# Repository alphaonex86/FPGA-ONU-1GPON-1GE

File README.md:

# FPGA-ONU

An open PON endpoint in one chip: 1 GPON/EPON ONU port (BOSA, to the ISP OLT), 1 SFP
cage (switch SFP, or EPON/GPON OLT module for the OLT role) and 1 Gigabit
Ethernet port, with the MACs, the Ethernet PHY and a RISC-V CPU integrated.
Developed and proven on an FPGA, the final target is an ASIC that holds everything.

## Goals

- GPON ONU MAC: GTC framing, FEC, AES-128 decryption, PLOAM, OMCI, upstream
  burst mode with DBA. EPON MAC (MPCP, OAM) and the OLT role of both.
- 1000BASE-T Ethernet port, PHY integrated in the target ASIC (FPGA phase: a
  copper SFP in an SFP+ cage on our HSMC card for the DE25-Standard; its other
  cage takes an OLT module or a normal SFP).
- SFP cage autodetects the module (EEPROM): 1000BASE-X, EPON OLT or GPON OLT.
- BOSA on board; all optics control (burst, APC, LOS, DDM) in the FPGA/ASIC
  logic; outside only analog: discrete RF transistors, a small ADC/DAC, the APD
  bias boost and passives (FPGA phase: an SY88236L BOSA driver on our HSMC
  card, straight to the DE25-Standard GTS transceivers).
- 32-bit RISC-V CPU (VexiiRiscv, rv32imac, no SIMD, no FPU), high energy
  efficiency, power management (clock gating, sleep states, DVFS); MMU (Sv32)
  so it runs Linux.
- Hardware acceleration (line rate, CPU off the data path): GPON, switching,
  VLAN, PPPoE, IPv4 and IPv6 routing, NAT.
- OpenWrt support: upstream-able riscv32 target, drivers for the GPON MAC and GE port.
- Firmware in an external, socketed, user-programmable flash.
- Behaves on the wire exactly like the stock ONU of each brand the OLT expects
  (ZTE, Huawei, ...): no unknown or unanswered message, no drop out of O5; the
  OLT side likewise mimics the stock OLT.
- ONU and OLT at once, each independent on its own segment; through software,
  the exchanges can be dumped and cloned into per-vendor profiles for everyone.
- Vendor-neutral RTL: vendor primitives only in thin wrappers, so the same tree
  goes from FPGA to ASIC.

## Layout

- `common/`: board-neutral parts: RTL and tests (`hw/`), KiCad generator and
  shared parts library (`pcb/gen`, `pcb/lib`).
- `agilex5/`: common to the Agilex 5 boards (Quartus benches, GTS lane variants).
- `de25-standard/`: Terasic DE25-Standard, our HSMC card (`pcb/hsmc`: two SFP+
  cages and the ONU BOSA; placed and routed, DRC/ERC clean, not yet ordered).
- `de25-nano/`: Terasic DE25-Nano, ECP5 SerDes bridge boards (alternative).

## Status

GPON OLT MAC in simulation (SpinalHDL): GTC downstream framer and deframer,
upstream burst receiver, ONU activation (serial number, ONU-ID, ranging, EqD)
with status-reporting DBA (DBRu), checked against G.984.3 vectors and Scala ONU models; the
OLT MAC top (311.04 / 155.52 MHz domains, CPU registers over APB with a
generated C header) meets timing on the DE25-Standard FPGA.
GPON ONU MAC in simulation: activation (O1-O7, TO1/TO2) with the fixed PLOAM set
in hardware (Acknowledge, Password, Alloc-ID and OMCI Port-ID), every other
PLOAM to the CPU, upstream burst framer timed to the bit from the downstream
frame (35 us response); checked in closed loop against our OLT MAC over a
simulated fibre (ranging, DBA, fibre cut and POPUP, Disable_Serial_Number),
and against the PLOAM sequences of real OLTs (ZTE as recorded by stock ONUs,
Broadcom Maple): every copy answered like the stock ONU, EqD drift updates to
the bit, deactivation churn; meets timing on the DE25-Standard FPGA. Like those
OLTs, our OLT sends each of its PLOAMs 3 times. OMCI over GEM both ways:
downstream fragments of the OMCI Port-ID to the CPU, CPU packets upstream in
the default allocation (OMCC), fragmented to the grant, and data GEM at the
same time in up to 4 data T-CONTs, each stream continuing its packet in its
next allocation. DBRu reports of the real backlog (reporting blocks rounded up,
G.984.3 Table 8-1 code, mode 0 and 1). Downstream AES-128
counter-mode decryption of the encrypted Port-IDs with the key switch at the
OLT's superframe, and downstream FEC: RS(255,239) decoding, up to 8 byte errors
corrected per codeword, with the counters of the OMCI FEC PM; checked against
the G.984.3 golden vectors (A.2.2, A.2.3 with FEC, A.3). The OLT sends
downstream FEC when enabled (CTRL register), every codeword's parity checked
against the model and decoded by our ONU in the closed loop. Upstream FEC in
the ONU when the OLT asks for it (Use_FEC): parity per codeword with the shorter
last one, the content sized to the data bytes, checked by a Scala OLT model; our
OLT does not ask for it (like Maple's default).
Ethernet port in simulation: comma alignment and 8b/10b on the raw 10-bit lane,
taxi's 1000BASE-X/SGMII PCS (autonegotiation) and 1G MAC (`common/hw/ext/taxi`,
submodule: `git submodule update --init`), two ports back to back; on the board
its own lane, SFP cage pins and HPS frame queues (`eth_board_regs.h`), checked
from the CPU registers to the looped-back lane.
L2 bridge GEM <-> Ethernet (`common/hw/spinal/pon/GemEthBridge.scala`,
`bridge_regs.h`): per Port-ID action towards Ethernet (drop, CPU, Ethernet;
whole frames with a good FCS), the outer VLAN ID or the untagged default picks
the Port-ID towards the PON, directly or by PCP (802.1p mapper), and the
Port-ID its T-CONT queue (4 on the ONU, each dropping when full without
blocking the others); VLAN treatments each way (G.988 ME 171 subset: push,
pop, translate, PCP set or kept; `VlanRewrite.scala`), the FCS computed after
the rewrite; store-and-forward queues across the four clocks, drops counted.
Flow offload in the bridge, each way (`FlowClassifier.scala`, mtk_ppe model):
frame parser (0-2 VLAN tags, PPPoE session, IPv4/IPv6 TCP/UDP), flow caches
keyed by the 5-tuple, outer VID and PPPoE session (2-way hash in block RAM,
written by the CPU, a hit bit per flow for the driver's stats: IPv4 2K flows
(1K on the board), IPv6 512, routed only, per direction), 64 egress entries (next hop and own MAC, PPPoE
session, VLAN treatment, Port-ID and queue); a hit is rewritten on its way out
(`FlowRewrite.scala`: MACs, PPPoE add/strip, NAPT, TTL or hop limit,
incremental IP and TCP/UDP checksums), a miss follows the L2 rules or, in flows mode (router: per
Port-ID or VLAN entry), goes to the CPU; on each board side the bridge's LAN and
WAN frame queues carry the misses to the CPU and the CPU's own frames out; control frames (ARP, PPPoE
discovery and LCP, DHCP, ICMPv6, IGMP, EAPOL, LLDP, slow protocols) get their own queues and interrupts
behind a token bucket per side, so a miss flood cannot delay them. On the board the Ethernet port goes to the CPU queues or to the
OLT or the ONU bridge (`eth_board_regs.h` BRIDGE); a frame from the lane reaches
the OLT MAC's downstream GEM, or the ONU MAC's upstream data stream, in
simulation; in the closed OLT <-> ONU loop, Ethernet frames cross both bridges
end to end each way, upstream in two T-CONTs granted by our OLT's DBA.
EPON MAC in simulation (`common/hw/spinal/pon/epon/`): clause 36 PCS (8b/10b,
comma sync at any bit slip) with the clause 65 LLID preamble and its CRC-8;
ONU MPCP (discovery with a random offset in the window, REGISTER_REQ/ACK,
timestamp sync and drift, GATE grants timed to the TQ with laser on/off and
sync time, REPORT, deregistration) and OLT MPCP (discovery windows, LLID
allocation, RTT per ONU, IPACT grants from the REPORTs within min/max, CPU and
timeout deregistration, the optics' receiver reset before each burst), checked
together over a simulated splitter with two
ONUs at different distances: no upstream collision, data per LLID each way.
Both MAC tops (`EponOnu.scala`, `EponOlt.scala`) run from their CPU registers
(`epon_onu_regs.h`, `epon_olt_regs.h`: configuration, registration state and
LLID, OLT events, frame counters, interrupts), checked through them alone;
on the DE25-Standard FPGA at 125 MHz: ONU 1.3K ALMs (211 MHz), OLT 2.5K ALMs
(141 MHz). With the same Ethernet bridges as GPON (`EponGem.scala`: the LLID is
the Port-ID, Port-ID 0xFFF the broadcast LLID; the ONU's REPORT from its queues),
Ethernet frames cross OLT port -> ONU port and back in simulation.
HSMC card GTS lanes (two SFP cages, ONU, burst enable) fit in Quartus at their
line rates from their refclk pins (`agilex5/gts/fit.sh`). One GTS dynamic
reconfiguration controller switches cage 0 and the ONU each on its own at run time
between GPON and 1.25 Gb/s, each profile on its own refclk: the cage 0 lane (GPON
OLT, or EPON OLT, 1000BASE-X or SGMII module) and the ONU BOSA lane with its
burst enable lane (EPON ONU); four combinations (GPON or 1.25 Gb/s per side), so
switching one side leaves the other running (to check on the board). Cage 0 with a normal SFP: the OLT core's own
Ethernet port replaces the EPON OLT MAC on the 1.25 Gb/s profile (`olt_board_regs.h`
ETH, set while the lane is reset; frames to the CPU queues at 0xA00), checked in
simulation through the lane; software picks the mode from the module's EEPROM.
Cage 1 is the Ethernet port's. In the board top the EPON MACs run on those profiles with the same bridges
and CPU queues, their registers on each side's bridge slave (0x800, the DR
controller's at 0x900 on the OLT's); the OLT's received words cross from each
profile's rx clock; the EPON ONU is loop-timed like the GPON one, by its own
VCXO loop on the 156.25 MHz VCXO; checked in simulation in both profiles.
Board top (`agilex5/hw/spinal/pon/PonBoard.scala`), OLT side: OLT MAC on its GTS lane
(2x oversampled upstream), HPS lightweight bridge to the MAC and board registers
(GTS reset/status, SFP cage pins, module I2C; `olt_board_regs.h`, `onu_board_regs.h`) and GEM CPU
queues for OMCI (whole packets downstream, upstream fragments with descriptors;
`gem_queues.h`). ONU side: ONU MAC on the BOSA data and burst enable lanes, its
clock kept on the recovered downstream clock by a VCXO loop (DDMTD phase
detector on a helper PLL, 6.7 ps steps, PI, sigma-delta: 0.03 bit of upstream
phase wander in simulation, the OLT tolerating 4), GEM CPU queues for OMCI,
optics pins with the laser held off until both lanes are up. Sniffer (ONU side, 0x900,
`sniffer_regs.h`; with a passive tap on a stock ONU's fibre, the BOSA receiving the downstream copy and a GPON
OLT module in cage 0 that ONU's bursts): one ONU's PLOAMs, BWmap
entries and GEM fragments (still ciphered) and its descrambled bursts, timestamped, read by the CPU as records;
the laser and cage 0's transmitter are held off while it records, and the module gets its burst reset before each
burst, planned from the captured BWmap; checked in simulation. HPS tool `common/sw/sniffer` (`make test`, `make
CC=aarch64-linux-gnu-gcc`): configures it from the exchange (ONU-ID, Alloc-IDs, OMCI Port-ID, delimiter), learns the
burst reset offset, writes raw records (`-w`, keep dumps out of this repo) and a decoded log, replays a dump (`-r`), waits on its interrupt
through UIO (`-u`, overlay from `de25-standard/ghrd/uio_overlay.sh`) or polls `/dev/mem`;
each burst is split by its matched grants into PLOAMu, DBRu and GEM frames, so the stock ONU's OMCI answers sit next
to the OLT's requests; `-P` writes them as an OMCI profile (whole messages paired by TCI: request, answer).
`common/sw/omci` (portable C, `make test`) loads such a profile and answers a request from it with the request's
TCI and a new trailer (AAL5 CRC-32): the clone path for MEs our ONU lacks.
`common/sw/linux` (GPL): the HPS driver of our ONU on the OpenWrt fork's GPON core (`make KDIR=...`): activation
stays in the FPGA, the core's OMCI responder answers on the OMCI Port-ID through the CPU GEM queues, and the core's
clone fallback answers what its ME model lacks from the binary profile (`common/sw/omci/omci_profile`). Not yet:
the Encryption_Key exchange, OMCI to bridge mapping.
Both sides checked in simulation, fit together on the DE25-Standard with the
HSMC card pins placed, flow engine, EPON OLT and ONU, cage 0's Ethernet port and the sniffer included: 40.5K ALMs (87 %), 308 of 358 M20K, setup slack +0.034 ns
(`agilex5/gts/fit.sh out/pon_board PonBoard`).
With the HPS: `de25-standard/ghrd/` brings Terasic's DE25-Standard reference design (GHRD, not in this
repository: `GHRD=<its folder> agilex5/gts/fit.sh <folder outside the repository> ghrd`) to Quartus 26.1, removes
its JTAG debug masters and shrinks its on-chip RAM to make room, and wires PonBoard in: its three register
windows on the HPS lightweight bridge (+0x100000 OLT, +0x101000 ONU, +0x102000 Ethernet), its 18 interrupts on
f2h_irq1 bits 0-17, its management clock the GHRD's 100 MHz: 42.7K ALMs (91 %), 312 of 358 M20K,
setup slack +0.017 ns. A fit folder holding an earlier fit made Quartus 26.1.1 crash (internal error 22912) or fail where a fresh
one passed, so fit.sh empties its own folder and refuses any other non-empty one. The HPS DDR settings were upgraded by Quartus: to check on the board.

## License

Hardware and RTL are licensed under the CERN Open Hardware Licence v2 -
Strongly Reciprocal ([CERN-OHL-S-2.0](LICENSE)). Exception: `common/sw/linux` (the Linux driver, built with the GPL GPON
core of the OpenWrt fork) is GPL-2.0-or-later.

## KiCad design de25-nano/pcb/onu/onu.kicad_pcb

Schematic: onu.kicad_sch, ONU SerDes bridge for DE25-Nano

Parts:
C1, C3, C6, C9, C24, C25, C30, C48, C49, C50, C51, C54, C57, C60, C63, C65, C76, C77, C83, C85: 10u; C_0603_1608Metric
C2, C4, C5, C7, C8, C10, C11: 22u; C_0805_2012Metric
C12, C13, C66, C67: 1u; C_0402_1005Metric
C14, C15, C16, C17, C18, C19, C20, C21, C22, C23, C26, C27, C28, C29, C31, C32, C33, C34, C35, C36, C37, C38, C39, C40, C41, C42, C43, C44, C45, C46, C47, C52, C53, C55, C56, C58, C59, C61, C62, C64, C68, C69, C70, C71, C72, C73, C74, C75, C78, C79, C80, C81, C82, C84, C93, C94: 100n; C_0402_1005Metric
C86, C87: 100n; C_0603_1608Metric; MPN 100 V X7R
C88: 220p; C_0603_1608Metric; MPN 100 V X7R
C89: 10n; C_0402_1005Metric; MPN 100 V X7R
C90: 2.2u; C_0603_1608Metric
C91, C92: 10p; C_0402_1005Metric
D1: BAT46WJ; D_SOD-323F; MPN BAT46WJ (100 V)
FB1, FB2, FB3, FB4, FB5, FB6, FB7, FB8, FB9: 120R@100MHz; L_0603_1608Metric; MPN BLM18PG121SN1D
H1, H2: M3; MountingHole_3.2mm_M3
J1: DE25-Nano GPIO; PinSocket_2x20_P2.54mm_Vertical
J2: JTAG; PinHeader_1x06_P2.54mm_Vertical
J3: OLT-ONU link; PinHeader_1x08_P2.54mm_Vertical
L1, L2: 2.2u; L_Cenker_CKCS252012; MPN SLO252012F2R2MTT
L3: 4.7u; L_Cenker_CKCS252012; MPN 4.7 uH, Isat >= 1 A, 2520
R1, R3: 100k; R_0402_1005Metric
R2, R4: 120k; R_0402_1005Metric
R5, R6, R7, R8, R9, R12, R13, R14, R19, R20: 4.7k; R_0402_1005Metric
R10, R15, R16, R24, R26, R37, R43: 10k; R_0402_1005Metric
R11, R30, R35: 1k; R_0402_1005Metric
R17, R18: 0; R_0402_1005Metric
R21: 5.1k; R_0402_1005Metric
R22: 6.2k; R_0402_1005Metric
R23, R38: 20k; R_0402_1005Metric
R25: 12k; R_0402_1005Metric
R27: 5.6k; R_0402_1005Metric
R28: 3.9k; R_0402_1005Metric
R29, R41: 1.5k; R_0402_1005Metric
R31, R33, R40: 10; R_0402_1005Metric
R32: 15; R_0402_1005Metric
R34: 100; R_0402_1005Metric
R36: 300k; R_0603_1608Metric
R39: 39k; R_0402_1005Metric
R42: 3.01k; R_0402_1005Metric
RN1, RN2, RN3, RN4, RN5: 22; R_Array_Convex_4x0402; MPN 4D02WGJ0220TCE
U1, U2: TLV62569DBVR; SOT-23-5; MPN TLV62569DBVR
U3: TLV75525PDBVR; SOT-23-5; MPN TLV75525PDBVR
U4: LFE5UM-25F-6BG381C; Lattice_caBGA-381_17x17mm_Layout20x20_P0.8mm; MPN LFE5UM-25F-6BG381C
U5: SY88236LMG; QFN-32-1EP_5x5mm_P0.5mm_EP3.1x3.1mm_ThermalVias; MPN SY88236LMG
U6: SN65LVDT2DBVR; SOT-23-5; MPN SN65LVDT2DBVR
U7: BOSA GPON (X100DG); BOSA_GPON; MPN desoldered from an X100DG; pad order to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
U8: TPS61391RTER; WQFN-16-1EP_3x3mm_P0.5mm_EP1.68x1.68mm_ThermalVias; MPN TPS61391RTER
U9: AD5593RBRUZ; TSSOP-16_4.4x5mm_P0.65mm; MPN AD5593RBRUZ
Y1: SiT3821 155.52 MHz; Oscillator_SMD_SiTime_SiT9121-6Pin_3.2x2.5mm; MPN SiT3821AI-2B2-33NB155.520000 (LVDS, +-5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

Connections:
+1V1: C7.1, C8.1, C14.1, C15.1, C16.1, C17.1, C18.1, C19.1, C20.1, C21.1, C22.1, C23.1, C24.1, C25.1, L1.2, R1.1, U4.H8 (VCC), U4.H9 (VCC), U4.H10 (VCC), U4.H11 (VCC), U4.H12 (VCC), U4.H13 (VCC), U4.J8 (VCC), U4.J13 (VCC), U4.K8 (VCC), U4.K13 (VCC), U4.L8 (VCC), U4.L13 (VCC), U4.M8 (VCC), U4.M13 (VCC), U4.N8 (VCC), U4.N9 (VCC), U4.N10 (VCC), U4.N11 (VCC), U4.N12 (VCC), U4.N13 (VCC)
+1V1_HRX: C58.1, C59.1, C60.1, FB4.2, U4.T8 (VCCHRX0_D0CH0), U4.T9 (VCCHRX1_D0CH1)
+1V1_HTX: C55.1, C56.1, C57.1, FB3.2, U4.T7 (VCCHTX0_D0CH0), U4.T10 (VCCHTX1_D0CH1)
+1V1_SD: C10.1, C11.1, FB2.1, FB3.1, FB4.1, L2.2, R3.1
+1V1_VCCA: C52.1, C53.1, C54.1, FB2.2, U4.T6 (VCCA0), U4.U6 (VCCA0)
+2V5: C13.1, FB1.1, FB5.1, U3.5 (OUT)
+2V5_AUX: C26.1, C27.1, C28.1, C29.1, C30.1, FB1.2, U4.F6 (VCCAUX), U4.F15 (VCCAUX), U4.P6 (VCCAUX), U4.P15 (VCCAUX)
+2V5_AUXA: C61.1, C62.1, C63.1, FB5.2, U4.V10 (VCCAUXA0), U4.V11 (VCCAUXA0)
+3V3: C3.1, C4.1, C5.1, C12.1, C31.1, C32.1, C33.1, C34.1, C35.1, C36.1, C37.1, C38.1, C39.1, C40.1, C41.1, C42.1, C43.1, C44.1, C45.1, C46.1, C47.1, C48.1, C49.1, C50.1, C51.1, C94.1, FB6.1, FB7.1, FB9.1, J1.29, J2.1, R5.2, R6.2, R7.2, R8.2, R9.2, R10.2, R11.2, R12.2, R13.2, R19.2, R20.2, R43.2, U3.1 (IN), U3.3 (EN), U4.F9 (VCCIO0), U4.F10 (VCCIO0), U4.F11 (VCCIO1), U4.F12 (VCCIO1), U4.H6 (VCCIO7), U4.H7 (VCCIO7), U4.H14 (VCCIO2), U4.H15 (VCCIO2), U4.J6 (VCCIO7), U4.J15 (VCCIO2), U4.L6 (VCCIO6), U4.L7 (VCCIO6), U4.L14 (VCCIO3), U4.L15 (VCCIO3), U4.M6 (VCCIO6), U4.M15 (VCCIO3), U4.P9 (VCCIO8), U4.P10 (VCCIO8), U9.3 (V_{DD}), U9.9 (V_{LOGIC})
+3V3_APD: C84.1, C85.1, FB9.2, L3.1, R40.1, U8.10 (VIN), U8.13 (EN)
+3V3_APDA: C90.1, R40.2, U8.14 (AVCC), U8.15 (AVCC)
+3V3_OPT: C72.1, C73.1, C74.1, C75.1, C76.1, C77.1, C78.1, FB7.2, FB8.1, R21.2, R32.2, U5.17 (VCC), U5.20 (VCC), U5.32 (VCC), U6.1 (VCC), U7.T1 (LD_A), U7.T4 (MPD_K)
+3V3_RX: C81.1, C82.1, C83.1, FB8.2, U7.R2 (VCC)
+3V3_XO: C64.1, C65.1, FB6.2, Y1.6 (VDD)
+5V: C1.1, C2.1, C6.1, C9.1, J1.11, U1.1 (EN), U1.4 (VIN), U2.1 (EN), U2.4 (VIN)
APCFAULT_N: U5.25 (~APCFAULT), U9.13 (IO7)
APCSET: R23.1, R24.1, U5.12 (APCSET)
APC_ADJ: R24.2, U9.4 (IO0)
APD_ADJ: R38.2, U9.6 (IO2)
APD_CAP: C89.1, U8.9 (CAP)
APD_FB: R36.2, R37.1, R38.1, U8.12 (FB)
APD_ISHORT: R39.1, U8.11 (ISHORT)
APD_MON: C91.1, R41.1, U8.4 (MON1), U9.11 (IO5)
APD_MON2: C92.1, R42.1, U8.3 (MON2)
BEN0: J1.15, U4.A13 (PT40B)
BEN1: J1.17, U4.A12 (PT40A)
BEN2: J1.19, U4.A11 (PT27B/PCLKC0_1)
BEN3: J1.20, U4.B10 (PT24B/GR_PCLK0_0)
BEN4: J1.21, U4.A8 (PT18B)
BEN5: J1.22, U4.B9 (PT22A)
BEN6: J1.24, U4.B8 (PT15B)
BEN7: J1.26, U4.A7 (PT18A)
BEN_N: R18.1, U4.W9 (HDTXN0_D0CH1)
BEN_P: R17.1, U4.W8 (HDTXP0_D0CH1)
BIASMAX: R27.1, U5.14 (BIASMAX)
BIASMON: R29.1, U5.23 (BIASMON), U9.7 (IO3)
CCLK: J3.4, R11.1, U4.U3 (CCLK)
CFG0: R5.1, U4.U4 (CFG_0)
DDM_RESET: R43.1, U9.1 (~RESET)
DDM_VREF: C93.1, U9.8 (V_{REF})
DONE: R8.1, U4.Y3 (DONE)
DS0: J1.13, RN4.5 (R4.2)
DS0_S: RN4.4 (R4.1), U4.A14 (PT47A)
DS1: J1.14, RN4.6 (R3.2)
DS1_S: RN4.3 (R3.1), U4.B13 (PT42A)
DS2: J1.16, RN4.7 (R2.2)
DS2_S: RN4.2 (R2.1), U4.B12 (PT35A/PCLKT1_0)
DS3: J1.18, RN4.8 (R1.2)
DS3_S: RN4.1 (R1.1), U4.B11 (PT29A/PCLKT0_0)
DS4: J1.23, RN3.5 (R4.2)
DS4_S: RN3.4 (R4.1), U4.A9 (PT24A/GR_PCLK0_1)
DS5: J1.27, RN3.6 (R3.2)
DS5_S: RN3.3 (R3.1), U4.B6 (PT4B)
DS6: J1.28, RN3.7 (R2.2)
DS6_S: RN3.2 (R2.1), U4.A6 (PT4A)
DS7: J1.31, RN3.8 (R1.2)
DS7_S: RN3.1 (R1.1), U4.B5 (PL2C)
DS8: J1.32, RN2.5 (R4.2)
DS8_S: RN2.4 (R4.1), U4.A5 (PL2B)
DS9: J1.33, RN2.6 (R3.2)
DS9_S: RN2.3 (R3.1), U4.B4 (PL5B)
DS10: J1.34, RN2.7 (R2.2)
DS10_S: RN2.2 (R2.1), U4.A4 (PL2A)
DS11: J1.35, RN2.8 (R1.2)
DS11_S: RN2.1 (R1.1), U4.B3 (PL5D)
DS12: J1.36, RN1.5 (R4.2)
DS12_S: RN1.4 (R4.1), U4.A3 (PL5C)
DS13: J1.37, RN1.6 (R3.2)
DS13_S: RN1.3 (R3.1), U4.B2 (PL14C/VREF1_7)
DS14: J1.38, RN1.7 (R2.2)
DS14_S: RN1.2 (R2.1), U4.A2 (PL14A)
DS15: J1.39, RN1.8 (R1.2)
DS15_S: RN1.1 (R1.1), U4.B1 (PL14B)
DS_CLK: J1.1, RN5.7 (R2.2)
DS_CLK_S: RN5.2 (R2.1), U4.B20 (PT67B)
FB_1V1: R1.2, R2.1, U1.5 (FB)
FB_1V1_SD: R3.2, R4.1, U2.5 (FB)
GND: C1.2, C2.2, C3.2, C4.2, C5.2, C6.2, C7.2, C8.2, C9.2, C10.2, C11.2, C12.2, C13.2, C14.2, C15.2, C16.2, C17.2, C18.2, C19.2, C20.2, C21.2, C22.2, C23.2, C24.2, C25.2, C26.2, C27.2, C28.2, C29.2, C30.2, C31.2, C32.2, C33.2, C34.2, C35.2, C36.2, C37.2, C38.2, C39.2, C40.2, C41.2, C42.2, C43.2, C44.2, C45.2, C46.2, C47.2, C48.2, C49.2, C50.2, C51.2, C52.2, C53.2, C54.2, C55.2, C56.2, C57.2, C58.2, C59.2, C60.2, C61.2, C62.2, C63.2, C64.2, C65.2, C66.2, C67.2, C72.2, C73.2, C74.2, C75.2, C76.2, C77.2, C78.2, C81.2, C82.2, C83.2, C84.2, C85.2, C86.2, C87.2, C88.2, C89.2, C90.2, C91.2, C92.2, C93.2, C94.2, J1.12, J1.30, J2.6, J3.1, J3.8, R2.2, R4.2, R14.2, R22.2, R23.2, R25.2, R27.2, R28.2, R29.2, R30.2, R37.2, R39.2, R41.2, R42.2, U1.2 (GND), U2.2 (GND), U3.2 (GND), U4.B7 (GND), U4.B14 (GND), U4.C19 (GND), U4.D4 (GND), U4.F7 (GND), U4.F8 (GND), U4.F13 (GND), U4.F14 (GND), U4.G4 (GND), U4.G6 (GND), U4.G7 (GND), U4.G8 (GND), U4.G9 (GND), U4.G10 (GND), U4.G11 (GND), U4.G12 (GND), U4.G13 (GND), U4.G14 (GND), U4.G15 (GND), U4.G17 (GND), U4.H19 (GND), U4.J2 (GND), U4.J7 (GND), U4.J9 (GND), U4.J10 (GND), U4.J11 (GND), U4.J12 (GND), U4.J14 (GND), U4.K6 (GND), U4.K7 (GND), U4.K9 (GND), U4.K10 (GND), U4.K11 (GND), U4.K12 (GND), U4.K14 (GND), U4.K15 (GND), U4.L9 (GND), U4.L10 (GND), U4.L11 (GND), U4.L12 (GND), U4.M2 (GND), U4.M7 (GND), U4.M9 (GND), U4.M10 (GND), U4.M11 (GND), U4.M12 (GND), U4.M14 (GND), U4.M16 (GND), U4.N6 (GND), U4.N7 (GND), U4.N14 (GND), U4.N15 (GND), U4.P7 (GND), U4.P8 (GND), U4.P11 (GND), U4.P12 (GND), U4.P13 (GND), U4.P14 (GND), U4.R4 (CFG_2), U4.R19 (GND), U4.T4 (CFG_1), U4.U7 (GND), U4.U8 (GND), U4.U9 (GND), U4.U10 (GND), U4.U11 (GND), U4.U12 (GND), U4.U13 (GND), U4.U14 (GND), U4.V5 (GND), U4.V6 (GND), U4.V7 (GND), U4.V8 (GND), U4.V9 (GND), U4.V12 (GND), U4.V13 (GND), U4.V14 (GND), U4.V15 (GND), U4.V16 (GND), U4.V19 (GND), U4.V20 (GND), U4.W6 (GND), U4.W7 (GND), U4.W12 (GND), U4.W15 (GND), U4.W16 (GND), U4.W19 (GND), U4.Y7 (HDRXP0_D0CH1), U4.Y8 (HDRXN0_D0CH1), U5.1 (LOS/SD_SEL), U5.5 (GND), U5.8 (GND), U5.16 (GND), U5.24 (GND), U5.29 (GND), U5.33 (EP), U6.2 (GND), U7.R5 (GND), U8.7 (GND), U8.16 (AGND), U8.17 (EP), U9.2 (A0), U9.14 (GND), Y1.3 (GND)
HOLDN: R10.1, U4.R2 (PB15A/HOLDN/DI/BUSY/CSSPIN/CEN)
HV_APD: C88.1, U7.R1 (VAPD), U8.5 (APD)
HV_FILT: C87.1, R34.2, R35.1
HV_MONIN: R35.2, U8.6 (MONIN)
HV_OUT: C86.1, D1.1 (K), R34.1, R36.1
HV_SW: D1.2 (A), L3.2, U8.8 (SW)
INITN: R7.1, U4.V3 (INITN)
LASER_DIS: R19.1, U4.U17 (PR47B), U5.11 (TXDIS)
LD_BEN: U5.9 (BEN+), U6.5 (R)
LD_BEN_N: R22.1, U5.10 (BEN-)
LD_BIAS: R33.1, U5.21 (BIAS)
LD_K: R31.2, R33.2, U7.T2 (LD_K)
LD_MD: U5.22 (MD), U7.T3 (MPD_A)
LD_MODN: R32.1, U5.18 (MOD-)
LD_MODP: R31.1, U5.19 (MOD+)
LOSLVL: R21.1, U5.2 (LOSLVL)
MISO: J3.6, U4.V2 (PB11A/D1/MISO/IO1)
MODMON: R28.1, U5.15 (MODMON), U9.10 (IO4)
MODSET: R25.1, R26.1, U5.13 (MODSET)
MOD_ADJ: R26.2, U9.5 (IO1)
MOSI: J3.5, U4.W2 (PB11B/D0/MOSI/IO0)
ONU_BEN_N: R18.2, U6.4 (B)
ONU_BEN_P: R17.2, U6.3 (A)
ONU_PROGRAMN: J3.7, R6.1, U4.W3 (PROGRAMN)
ONU_RD_N: C71.1, U5.30 (ROUT-)
ONU_RD_P: C70.1, U5.31 (ROUT+)
ONU_SCL: J3.2, U9.16 (SCL)
ONU_SDA: J3.3, U9.15 (SDA)
ONU_TD_N: C69.2, U5.6 (DIN+)
ONU_TD_P: C68.2, U5.7 (DIN-)
REFCLK_N: U4.Y12 (REFCLKN_D0), Y1.5 (OUT-)
REFCLK_P: U4.Y11 (REFCLKP_D0), Y1.4 (OUT+)
RIN_N: C80.2, U5.28 (RIN-)
RIN_P: C79.2, U5.27 (RIN+)
RSSI: R30.1, U5.26 (RSSI), U9.12 (IO6)
RX0_N: C71.2, U4.Y6 (HDRXN0_D0CH0)
RX0_P: C70.2, U4.Y5 (HDRXP0_D0CH0)
RX_SD: R20.1, U4.T17 (PR47D/LRC_GPLL0C_IN), U5.3 (LOS/SD), U5.4 (~JAM)
SN: J1.40, R9.1, U4.T2 (PB13A/SN/CSN)
SW_1V1: L1.1, U1.3 (SW)
SW_1V1_SD: L2.1, U2.3 (SW)
TCK: J2.2, R14.1, U4.T5 (TCK)
TDI: J2.3, R12.1, U4.R5 (TDI)
TDO: J2.4, U4.V4 (TDO)
TIA_N: C80.1, U7.R4 (OUT-)
TIA_P: C79.1, U7.R3 (OUT+)
TMS: J2.5, R13.1, U4.U5 (TMS)
TX0_N: C69.1, U4.W5 (HDTXN0_D0CH0)
TX0_P: C68.1, U4.W4 (HDTXP0_D0CH0)
TX_CLK: J1.3, RN5.8 (R1.2)
TX_CLK_S: RN5.1 (R1.1), U4.A19 (PT67A)
US0: J1.2, U4.B19 (PT65B)
US1: J1.4, U4.B18 (PT62B)
US2: J1.5, U4.A18 (PT65A)
US3: J1.6, U4.B17 (PT60A)
US4: J1.7, U4.A17 (PT62A)
US5: J1.8, U4.B16 (PT56B)
US6: J1.9, U4.A16 (PT56A)
US7: J1.10, U4.B15 (PT51A)
US_CLK: J1.25, U4.A10 (PT27A/PCLKT0_1)
VCXO_PWM: R15.1, U4.U16 (PR47C/LRC_GPLL0T_IN)
VCXO_RC: C66.1, R15.2, R16.1
VCXO_VC: C67.1, R16.2, Y1.1 (VIN)

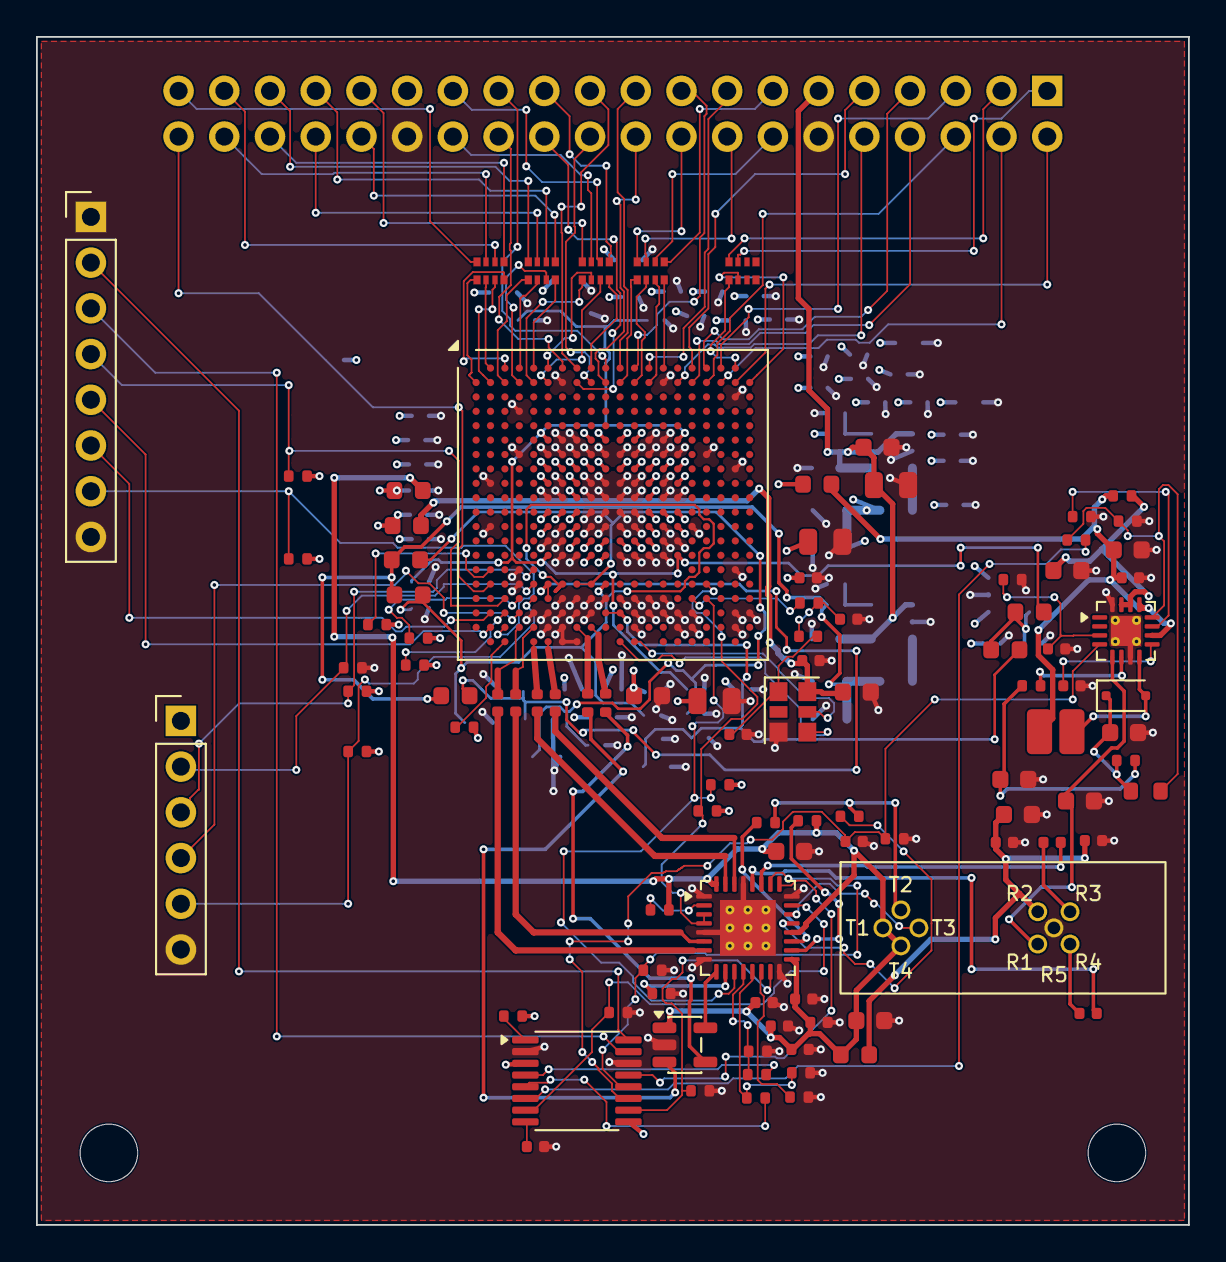
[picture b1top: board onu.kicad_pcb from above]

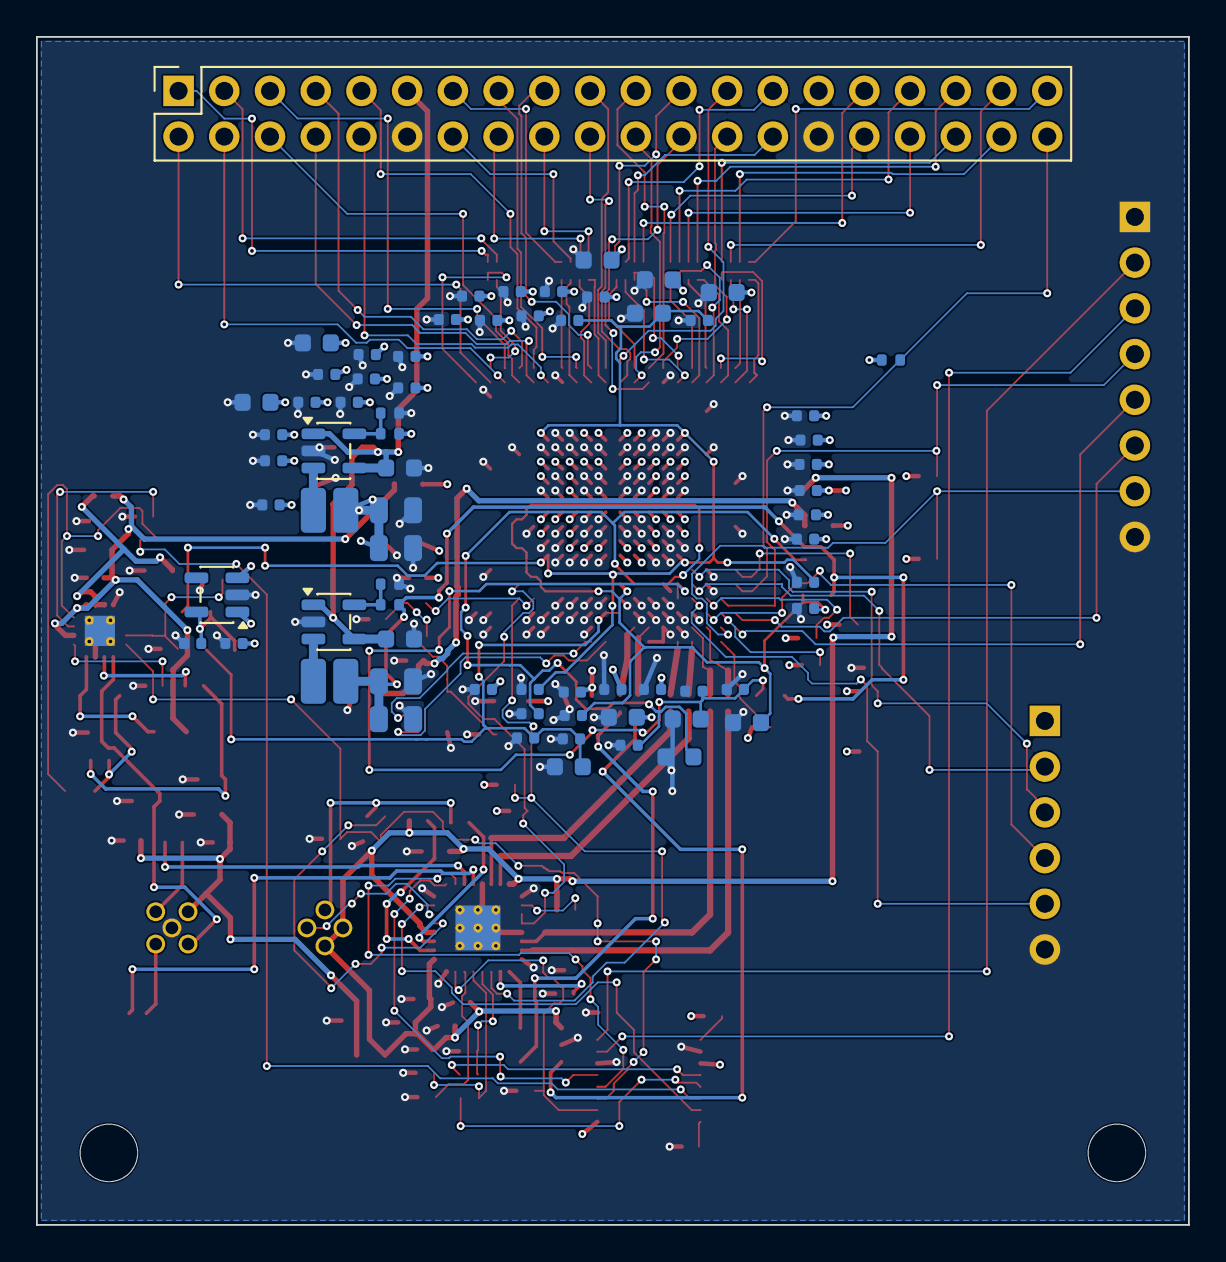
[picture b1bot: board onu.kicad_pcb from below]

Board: 4 copper layers, 64.0 x 66.0 mm, 170 parts (69 on the bottom side), 141 nets.

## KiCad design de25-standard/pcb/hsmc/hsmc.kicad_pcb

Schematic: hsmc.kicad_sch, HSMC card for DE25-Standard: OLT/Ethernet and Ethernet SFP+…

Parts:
C1, C2, C7, C8, C11, C12, C15, C16, C18, C25, C27, C30, C32, C35, C36, C37, C38, C39, C40, C41, C42, C45, C46, C47, C48, C49, C51, C60, C61, C63, C65, C66: 100n; C_0402_1005Metric
C3, C4, C17, C26, C28, C31, C33, C43, C44, C50, C52: 10u; C_0603_1608Metric
C5, C6, C22, C23, C24, C29, C34: 22u; C_0805_2012Metric
C9, C10, C13, C14: 1u; C_0402_1005Metric
C19, C20: 10u; C_0805_2012Metric; MPN 10 uF 25 V X5R 0805
C21: 100n; C_0603_1608Metric; MPN 100 nF 25 V
C53, C54: 100n; C_0603_1608Metric; MPN 100 V X7R
C55: 220p; C_0603_1608Metric; MPN 100 V X7R
C56: 10n; C_0402_1005Metric; MPN 100 V X7R
C57: 2.2u; C_0603_1608Metric
C58, C59: 10p; C_0402_1005Metric
C62: 100n; C_0603_1608Metric; MPN 100 nF 50 V X7R 0603
C64: 47p; C_0402_1005Metric
D1: BAT46WJ; D_SOD-323F; MPN BAT46WJ (100 V)
FB1, FB2, FB3, FB4: 120R@100MHz; L_0603_1608Metric; MPN BLM18PG121SN1D
H1, H2: M3; MountingHole_3.2mm_M3
J1: ASP-122952-01; HSMC_ASP-122952-01; MPN Samtec ASP-122952-01
J2: SFP0 cage; Connector_SFP_and_Cage; MPN SFP+ cage (SFF-8432) + 20-pin host conn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
J3: SFP1 cage; Connector_SFP_and_Cage; MPN SFP+ cage (SFF-8432) + 20-pin host conn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
L1: 2.2u; L_Cenker_CKCS4020; MPN 2.2 uH, Isat >= 4 A, 4020
L2, L3, L4, L5: 1u; L_0805_2012Metric; MPN 1 uH >= 1 A, low DCR
L6: 4.7u; L_Cenker_CKCS252012; MPN 4.7 uH, Isat >= 1 A, 2520
R1, R2, R5, R6: 150; R_0402_1005Metric
R3, R4, R7, R8, R10, R32, R34, R45, R51: 10k; R_0402_1005Metric
R9: 33.2k; R_0402_1005Metric
R11, R19: 33; R_0402_1005Metric
R12, R20: 330; R_0402_1005Metric
R13, R14, R15, R16, R17, R18, R21, R22, R23, R24, R25, R26, R27, R28, R52, R53, R57: 4.7k; R_0402_1005Metric
R29: 5.1k; R_0402_1005Metric
R30: 6.2k; R_0402_1005Metric
R31, R46: 20k; R_0402_1005Metric
R33: 12k; R_0402_1005Metric
R35: 5.6k; R_0402_1005Metric
R36: 3.9k; R_0402_1005Metric
R37, R49: 1.5k; R_0402_1005Metric
R38, R43, R56: 1k; R_0402_1005Metric
R39, R41, R48: 10; R_0402_1005Metric
R40: 15; R_0402_1005Metric
R42: 100; R_0402_1005Metric
R44: 300k; R_0603_1608Metric
R47: 39k; R_0402_1005Metric
R50: 3.01k; R_0402_1005Metric
R54: 0; R_0402_1005Metric; not fitted
R55: 15k; R_0402_1005Metric
R58, R59, R60, R61: 20; R_0402_1005Metric
U1: TPS563201DDCR; SOT-23-6; MPN TPS563201DDCR
U2: SY88236LMG; QFN-32-1EP_5x5mm_P0.5mm_EP3.1x3.1mm_ThermalVias; MPN SY88236LMG
U3: SN65LVDT2DBVR; SOT-23-5; MPN SN65LVDT2DBVR
U4: BOSA GPON (X100DG); BOSA_GPON; MPN desoldered from an X100DG; pad order to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
U5: TPS61391RTER; WQFN-16-1EP_3x3mm_P0.5mm_EP1.68x1.68mm_ThermalVias; MPN TPS61391RTER
U6: AD5593RBRUZ; TSSOP-16_4.4x5mm_P0.65mm; MPN AD5593RBRUZ
U7: SN74LVC1G123DCUR; VSSOP-8_2.3x2mm_P0.5mm; MPN SN74LVC1G123DCUR
U8: SN74LVC1G97DBVR; SOT-23-6; MPN SN74LVC1G97DBVR
U9: SN74LVC1G32DBVR; SOT-23-5; MPN SN74LVC1G32DBVR
Y1: SiT3821 156.25 MHz; Oscillator_SMD_SiTime_SiT9121-6Pin_3.2x2.5mm; MPN SiT3821AI-1B2-33NH156.250000
Y2: SiT3821 155.52 MHz; Oscillator_SMD_SiTime_SiT9121-6Pin_3.2x2.5mm; MPN SiT3821AI-1B2-33NE155.520000

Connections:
+3V3: C1.1, C2.1, C3.1, C4.1, C5.1, C6.1, C61.1, C63.1, C65.1, C66.1, FB1.1, FB2.1, FB4.1, J1.45 (3.3V), J1.51 (3.3V), J1.57 (3.3V), J1.63 (3.3V), J1.69 (3.3V), J1.75 (3.3V), J1.81 (3.3V), J1.87 (3.3V), J1.93 (3.3V), J1.99 (3.3V), J1.105 (3.3V), J1.111 (3.3V), J1.117 (3.3V), J1.123 (3.3V), J1.129 (3.3V), J1.135 (3.3V), J1.141 (3.3V), J1.147 (3.3V), J1.153 (3.3V), J1.159 (3.3V), R27.2, R28.2, R51.2, R52.2, R53.2, R55.2, R57.2, U6.3 (V_{DD}), U6.9 (V_{LOGIC}), U7.3 (~CLR), U7.8 (VCC), U8.5 (VCC), U9.5 (VCC)
+3V3_APD: C51.1, C52.1, FB4.2, L6.1, R48.1, U5.10 (VIN), U5.13 (EN)
+3V3_APDA: C57.1, R48.2, U5.14 (AVCC), U5.15 (AVCC)
+3V3_OPT: C39.1, C40.1, C41.1, C42.1, C43.1, C44.1, C45.1, FB2.2, FB3.1, R29.2, R40.2, U2.17 (VCC), U2.20 (VCC), U2.32 (VCC), U3.1 (VCC), U4.T1 (LD_A), U4.T4 (MPD_K)
+3V3_RX: C48.1, C49.1, C50.1, FB3.2, U4.R2 (VCC)
+3V3_SFP: C22.1, C23.1, C24.1, C29.1, C34.1, L1.2, L2.1, L3.1, L4.1, L5.1, R9.1, R13.2, R14.2, R15.2, R16.2, R17.2, R18.2, R21.2, R22.2, R23.2, R24.2, R25.2, R26.2
+3V3_SFP0R: C27.1, C28.1, J2.15 (VccR), L3.2
+3V3_SFP0T: C25.1, C26.1, J2.16 (VccT), L2.2
+3V3_SFP1R: C32.1, C33.1, J3.15 (VccR), L5.2
+3V3_SFP1T: C30.1, C31.1, J3.16 (VccT), L4.2
+3V3_XO: C15.1, C16.1, C17.1, FB1.2, Y1.6 (VDD), Y2.6 (VDD)
+12V: C19.1, C20.1, C21.1, J1.88 (12V), J1.94 (12V), J1.100 (12V), U1.3 (VIN), U1.5 (EN)
APCFAULT_N: U2.25 (~APCFAULT), U6.13 (IO7)
APCSET: R31.1, R32.1, U2.12 (APCSET)
APC_ADJ: R32.2, U6.4 (IO0)
APD_ADJ: R46.2, U6.6 (IO2)
APD_CAP: C56.1, U5.9 (CAP)
APD_FB: R44.2, R45.1, R46.1, U5.12 (FB)
APD_ISHORT: R47.1, U5.11 (ISHORT)
APD_MON: C58.1, R49.1, U5.4 (MON1), U6.11 (IO5)
APD_MON2: C59.1, R50.1, U5.3 (MON2)
BEN_DLY: C64.1, R56.2, U8.1 (IN1)
BEN_IO: J1.120 (LVDS_RXp11), R54.1
BIASMAX: R35.1, U2.14 (BIASMAX)
BIASMON: R37.1, U2.23 (BIASMON), U6.7 (IO3)
BST_SFP: C18.1, U1.6 (VBST)
BURST_CUT: J1.116 (LVDS_RXn10), U8.4 (Y), U9.2
CUT_C: C62.1, U7.6 (Cext)
CUT_Q: U7.5 (Q), U8.6 (IN2)
CUT_RC: C62.2, R55.1, U7.7 (RCext)
DDM_RESET: R51.1, U6.1 (~RESET)
DDM_VREF: C60.1, U6.8 (V_{REF})
FB_SFP: R9.2, R10.1, U1.4 (VFB)
GND: C1.2, C2.2, C3.2, C4.2, C5.2, C6.2, C9.2, C10.2, C13.2, C14.2, C15.2, C16.2, C17.2, C19.2, C20.2, C21.2, C22.2, C23.2, C24.2, C25.2, C26.2, C27.2, C28.2, C29.2, C30.2, C31.2, C32.2, C33.2, C34.2, C39.2, C40.2, C41.2, C42.2, C43.2, C44.2, C45.2, C48.2, C49.2, C50.2, C51.2, C52.2, C53.2, C54.2, C55.2, C56.2, C57.2, C58.2, C59.2, C60.2, C61.2, C63.2, C64.2, C65.2, C66.2, J1.160 (PSNTn), J1.161 (GND), J1.162 (GND), J1.163 (GND), J1.164 (GND), J1.165 (GND), J1.166 (GND), J1.167 (GND), J1.168 (GND), J1.169 (GND), J1.170 (GND), J1.171 (GND), J1.172 (GND), J2.1 (VeeT), J2.10 (VeeR), J2.11 (VeeR), J2.14 (VeeR), J2.17 (VeeT), J2.20 (VeeT), J2.CAGE, J3.1 (VeeT), J3.10 (VeeR), J3.11 (VeeR), J3.14 (VeeR), J3.17 (VeeT), J3.20 (VeeT), J3.CAGE, R1.2, R2.2, R5.2, R6.2, R10.2, R30.2, R31.2, R33.2, R35.2, R36.2, R37.2, R38.2, R45.2, R47.2, R49.2, R50.2, U1.1 (GND), U2.1 (LOS/SD_SEL), U2.5 (GND), U2.8 (GND), U2.16 (GND), U2.24 (GND), U2.29 (GND), U2.33 (EP), U3.2 (GND), U4.R5 (GND), U5.7 (GND), U5.16 (AGND), U5.17 (EP), U6.2 (A0), U6.14 (GND), U7.1 (~A), U7.4 (GND), U8.2 (GND), U8.3 (IN0), U9.3 (GND), Y1.3 (GND), Y2.3 (GND)
GTS_REFCLK_AC_N: C8.2, R59.1
GTS_REFCLK_AC_P: C7.2, R58.1
GTS_REFCLK_N: J1.8 (XCVR_RXn6), R59.2
GTS_REFCLK_P: J1.6 (XCVR_RXp6), R58.2
GTS_RXREF_AC_N: C12.2, R61.1
GTS_RXREF_AC_P: C11.2, R60.1
GTS_RXREF_N: J1.4 (XCVR_RXn7), R61.2
GTS_RXREF_P: J1.2 (XCVR_RXp7), R60.2
HV_APD: C55.1, U4.R1 (VAPD), U5.5 (APD)
HV_FILT: C54.1, R42.2, R43.1
HV_MONIN: R43.2, U5.6 (MONIN)
HV_OUT: C53.1, D1.1 (K), R42.1, R44.1
HV_SW: D1.2 (A), L6.2, U5.8 (SW)
LASER_DIS: R27.1, U2.11 (TXDIS), U9.4
LASER_DIS_FPGA: J1.102 (LVDS_RXp8), R57.1, U9.1
LD_BEN: R54.2, R56.1, U2.9 (BEN+), U3.5 (R), U7.2 (B)
LD_BEN_N: R30.1, U2.10 (BEN-)
LD_BIAS: R41.1, U2.21 (BIAS)
LD_K: R39.2, R41.2, U4.T2 (LD_K)
LD_MD: U2.22 (MD), U4.T3 (MPD_A)
LD_MODN: R40.1, U2.18 (MOD-)
LD_MODP: R39.1, U2.19 (MOD+)
LOSLVL: R29.1, U2.2 (LOSLVL)
MODMON: R36.1, U2.15 (MODMON), U6.10 (IO4)
MODSET: R33.1, R34.1, U2.13 (MODSET)
MOD_ADJ: R34.2, U6.5 (IO1)
ONU_BEN_N: J1.31 (XCVR_TXn0), U3.4 (B)
ONU_BEN_P: J1.29 (XCVR_TXp0), U3.3 (A)
ONU_RD_N: C38.1, U2.30 (ROUT-)
ONU_RD_P: C37.1, U2.31 (ROUT+)
ONU_RX_N: C38.2, J1.26 (XCVR_RXp1)
ONU_RX_P: C37.2, J1.28 (XCVR_RXn1)
ONU_SCL: J1.108 (LVDS_RXp9), R52.1, U6.16 (SCL)
ONU_SDA: J1.110 (LVDS_RXn9), R53.1, U6.15 (SDA)
ONU_TD_N: C36.2, U2.6 (DIN+)
ONU_TD_P: C35.2, U2.7 (DIN-)
ONU_TX_N: C36.1, J1.25 (XCVR_TXp1)
ONU_TX_P: C35.1, J1.27 (XCVR_TXn1)
RIN_N: C47.2, U2.28 (RIN-)
RIN_P: C46.2, U2.27 (RIN+)
RSSI: R38.1, U2.26 (RSSI), U6.12 (IO6)
RX_SD: J1.104 (LVDS_RXn8), R28.1, U2.3 (LOS/SD), U2.4 (~JAM)
SFP0_LOS: J1.48 (LVDS_RXp0), J2.8 (RX_LOS), R15.1
SFP0_MOD_ABS: J1.50 (LVDS_RXn0), J2.6 (MOD_ABS), R16.1
SFP0_P7: J2.7 (RS0), R11.2
SFP0_P9: J2.9 (RS1), R12.2
SFP0_RD_N: J1.18 (XCVR_RXp3), J2.12 (RD-)
SFP0_RD_P: J1.20 (XCVR_RXn3), J2.13 (RD+)
SFP0_RS0: J1.60 (LVDS_RXp2), R11.1
SFP0_RS1: J1.62 (LVDS_RXn2), R12.1
SFP0_SCL: J1.54 (LVDS_RXp1), J2.5 (SCL), R17.1
SFP0_SDA: J1.56 (LVDS_RXn1), J2.4 (SDA), R18.1
SFP0_TD_N: J1.19 (XCVR_TXn3), J2.19 (TD-)
SFP0_TD_P: J1.17 (XCVR_TXp3), J2.18 (TD+)
SFP0_TX_DIS: J1.42 (D1), J2.3 (TX_DISABLE), R14.1
SFP0_TX_FAULT: J1.44 (D3), J2.2 (TX_FAULT), R13.1
SFP1_LOS: J1.72 (LVDS_RXp4), J3.8 (RX_LOS), R23.1
SFP1_MOD_ABS: J1.74 (LVDS_RXn4), J3.6 (MOD_ABS), R24.1
SFP1_P7: J3.7 (RS0), R19.2
SFP1_P9: J3.9 (RS1), R20.2
SFP1_RD_N: J1.22 (XCVR_RXp2), J3.12 (RD-)
SFP1_RD_P: J1.24 (XCVR_RXn2), J3.13 (RD+)
SFP1_RS0: J1.84 (LVDS_RXp6), R19.1
SFP1_RS1: J1.86 (LVDS_RXn6), R20.1
SFP1_SCL: J1.78 (LVDS_RXp5), J3.5 (SCL), R25.1
SFP1_SDA: J1.80 (LVDS_RXn5), J3.4 (SDA), R26.1
SFP1_TD_N: J1.23 (XCVR_TXn2), J3.19 (TD-)
SFP1_TD_P: J1.21 (XCVR_TXp2), J3.18 (TD+)
SFP1_TX_DIS: J1.66 (LVDS_RXp3), J3.3 (TX_DISABLE), R22.1
SFP1_TX_FAULT: J1.68 (LVDS_RXn3), J3.2 (TX_FAULT), R21.1
SW_SFP: C18.2, L1.1, U1.2 (SW)
TIA_N: C47.1, U4.R4 (OUT-)
TIA_P: C46.1, U4.R3 (OUT+)
VCXO156_N: C8.1, R2.1, Y1.5 (OUT-)
VCXO156_P: C7.1, R1.1, Y1.4 (OUT+)
VCXO156_PWM: J1.122 (LVDS_RXn11), R3.1
VCXO156_RC: C9.1, R3.2, R4.1
VCXO156_VC: C10.1, R4.2, Y1.1 (VIN)
VCXO_N: C12.1, R6.1, Y2.5 (OUT-)
VCXO_P: C11.1, R5.1, Y2.4 (OUT+)
VCXO_PWM: J1.114 (LVDS_RXp10), R7.1
VCXO_RC: C13.1, R7.2, R8.1
VCXO_VC: C14.1, R8.2, Y2.1 (VIN)

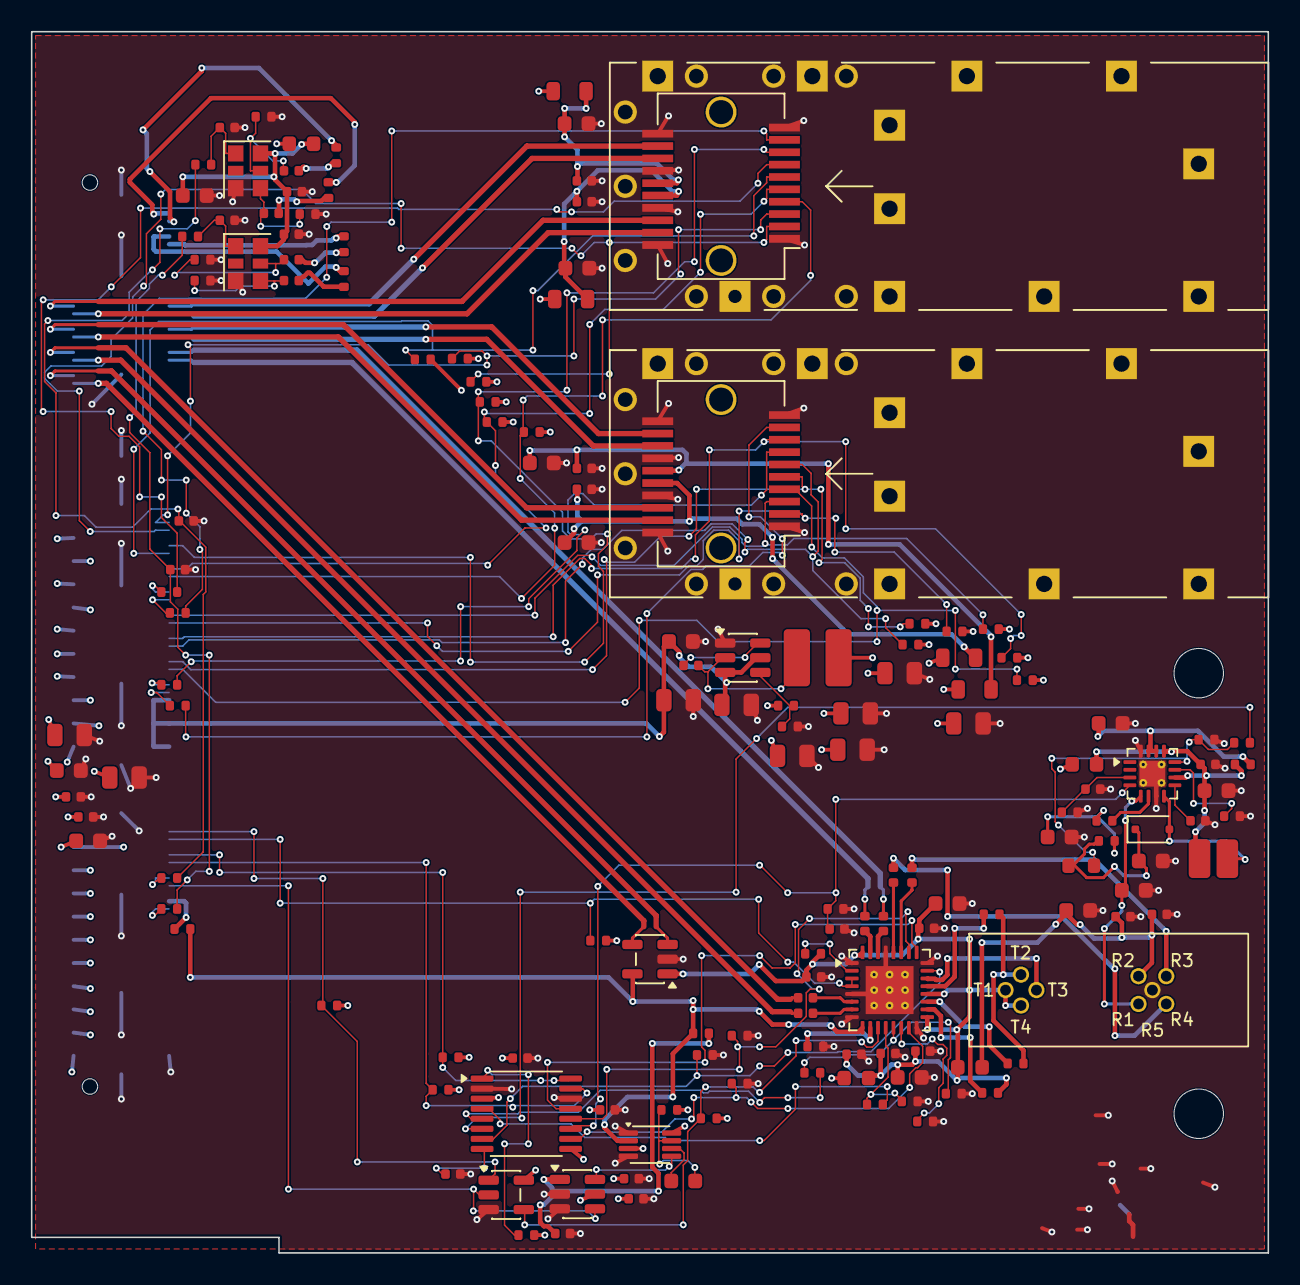
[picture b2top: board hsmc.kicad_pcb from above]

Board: 4 copper layers, 80.0 x 79.0 mm, 154 parts (1 on the bottom side), 117 nets.
